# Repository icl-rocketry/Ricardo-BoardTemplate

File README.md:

# Ricardo Board Template
This is a KiCad template including the required components for an ESP32S3 with a USB-C port, a CAN transceiver, as well as logic power input regulation. This is the bare minimum needed for boards in the ricardo ecosystem. If you have followed the [hardware library usage instructions](https://github.com/icl-rocketry/iclr-hw), the hardware libraries will automatically be added to every project started from this template.

## Usage
To use this, clone this repository in your KiCad user templates folder.

By default, this folder is:

MacOS - ```/Users/{USERNAME}/Documents/KiCad/8.0/template/```

Windows -  ```%USERPROFILE%/Documents/KiCad/8.0/template```

Linux - ```/home/{USERNAME}/.local/share/kicad/8.0/template```

Then, you will be able to access the template when making a new project in ```KiCad -> File -> New Project from Template... -> User Templates```

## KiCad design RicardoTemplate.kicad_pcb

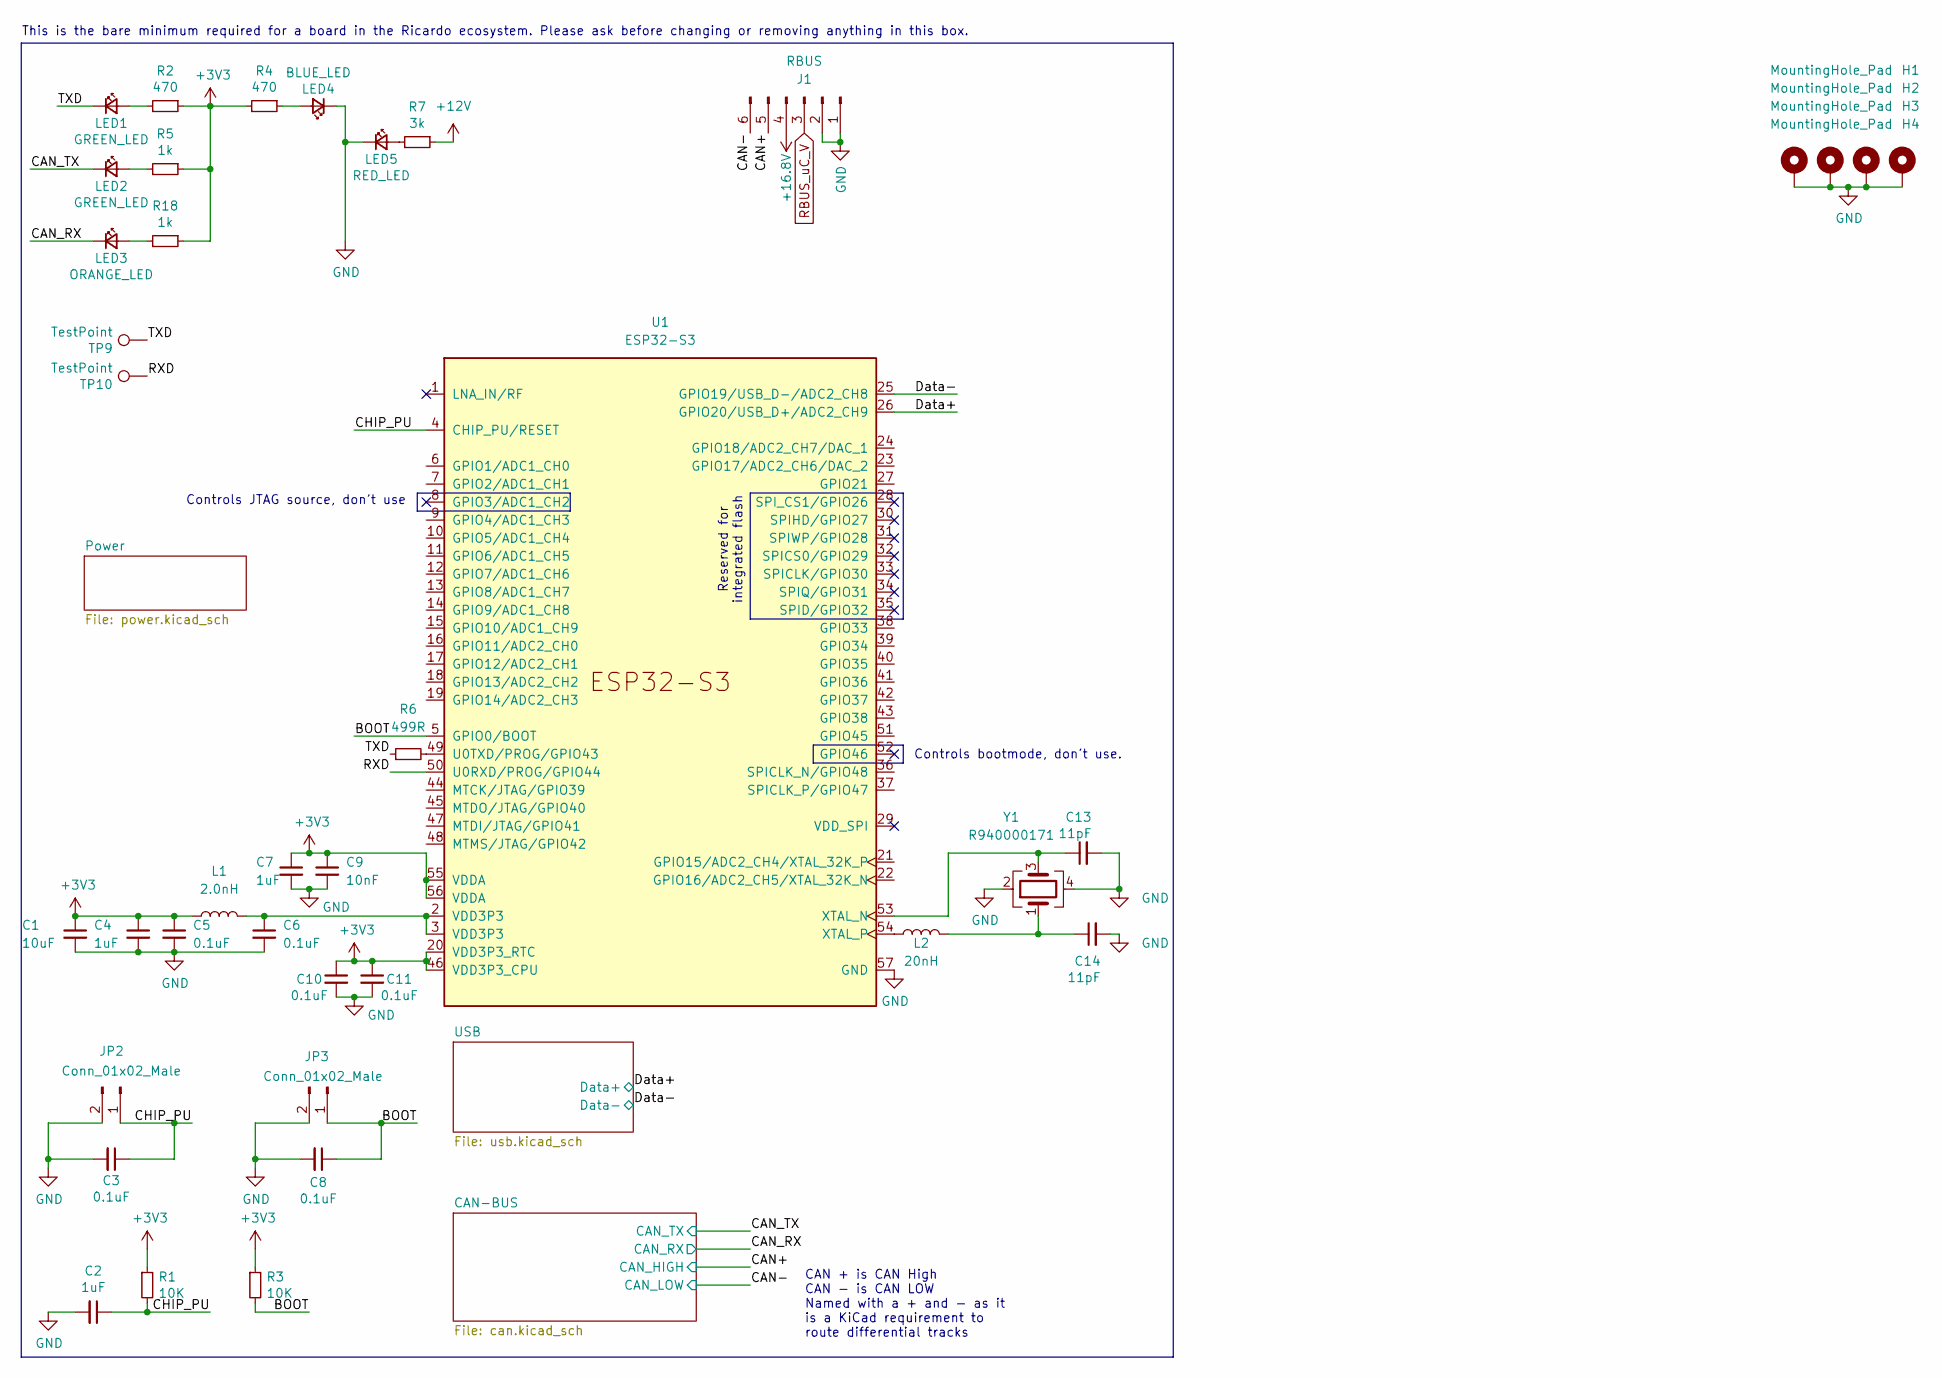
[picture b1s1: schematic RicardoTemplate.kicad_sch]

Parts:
C1: 10uF; C_0402_1005Metric
C2, C4, C7: 1uF; C_0402_1005Metric
C3, C5, C6, C8, C10, C11: 0.1uF; C_0402_1005Metric
C9: 10nF; C_0402_1005Metric
C13, C14: 11pF; C_0402_1005Metric
H1, H2, H3, H4: MountingHole_Pad; MountingHole_3.2mm_M3_DIN965_Pad
J1: RBUS; Molex_Mini-Fit_Jr_5569-06A2_2x03_P4.20mm_Horizontal
JP2, JP3: Conn_01x02_Male; PinHeader_1x02_P2.54mm_Vertical
L1: 2.0nH; L_0402_1005Metric
L2: 20nH; L_0402_1005Metric
LED1, LED2: GREEN_LED; LED_0402_1005Metric
LED3: ORANGE_LED; LED_0402_1005Metric
LED4: BLUE_LED; LED_0402_1005Metric
LED5: RED_LED; LED_0402_1005Metric
R1, R3: 10K; R_0402_1005Metric
R2, R4: 470; R_0402_1005Metric
R5, R18: 1k; R_0402_1005Metric
R6: 499R; R_0402_1005Metric
R7: 3k; R_0402_1005Metric
TP9, TP10: TestPoint; TestPoint_Pad_D1.0mm
U1: ESP32-S3; QFN40P700X700X90-57N
Y1: R940000171; Crystal_SMD_2016-4Pin_2.0x1.6mm

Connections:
+3V3: C1.1, C4.1, C5.1, C7.1, C9.1, C10.1, C11.1, L1.1, R1.1, R2.1, R3.1, R4.2, R5.1, R18.1, U1.20 (VDD3P3_RTC), U1.46 (VDD3P3_CPU), U1.55 (VDDA), U1.56 (VDDA); also elsewhere on the board
+12V: R7.1
+16.8V: J1.4
/BOOT: C8.1, JP3.1, R3.2, U1.5 (GPIO0/BOOT)
/CAN+: J1.5; also elsewhere on the board
/CAN-: J1.6; also elsewhere on the board
/CAN_RX: LED3.1 (K); also elsewhere on the board
/CAN_TX: LED2.1 (K); also elsewhere on the board
/CHIP_PU: C2.1, C3.1, JP2.1, R1.2, U1.4 (CHIP_PU/RESET)
/Data+: U1.26 (GPIO20/USB_D+/ADC2_CH9); also elsewhere on the board
/Data-: U1.25 (GPIO19/USB_D-/ADC2_CH8); also elsewhere on the board
/RXD: TP10.1, U1.50 (U0RXD/PROG/GPIO44)
/TXD: LED1.1 (K), R6.1, TP9.1
GND: C1.2, C2.2, C3.2, C4.2, C5.2, C6.2, C7.2, C8.2, C9.2, C10.2, C11.2, C13.2, C14.2, H1.1, H2.1, H3.1, H4.1, J1.1, J1.2, JP2.2, JP3.2, LED4.1 (K), LED5.1 (K), U1.57 (GND), Y1.2, Y1.4; also elsewhere on the board
unnamed: C6.1, L1.2, U1.2 (VDD3P3), U1.3 (VDD3P3)
unnamed: C14.1, L2.2, Y1.1
unnamed: LED1.2 (A), R2.2
unnamed: LED2.2 (A), R5.2
unnamed: LED3.2 (A), R18.2
unnamed: LED4.2 (A), R4.1
unnamed: LED5.2 (A), R7.2
unnamed: R6.2, U1.49 (U0TXD/PROG/GPIO43)
unnamed: C13.1, U1.53 (XTAL_N), Y1.3
unnamed: L2.1, U1.54 (XTAL_P)
RBUS_uC_V: J1.3; also elsewhere on the board

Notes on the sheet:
Controls bootmode, don't use.
This is the bare minimum required for a board in the Ricardo ecosystem. Please ask before changing or removing anything in this box.
CAN + is CAN High CAN - is CAN LOW Named with a + and - as it is a KiCad requirement to route differential tracks
Controls JTAG source, don't use
Reserved for integrated flash

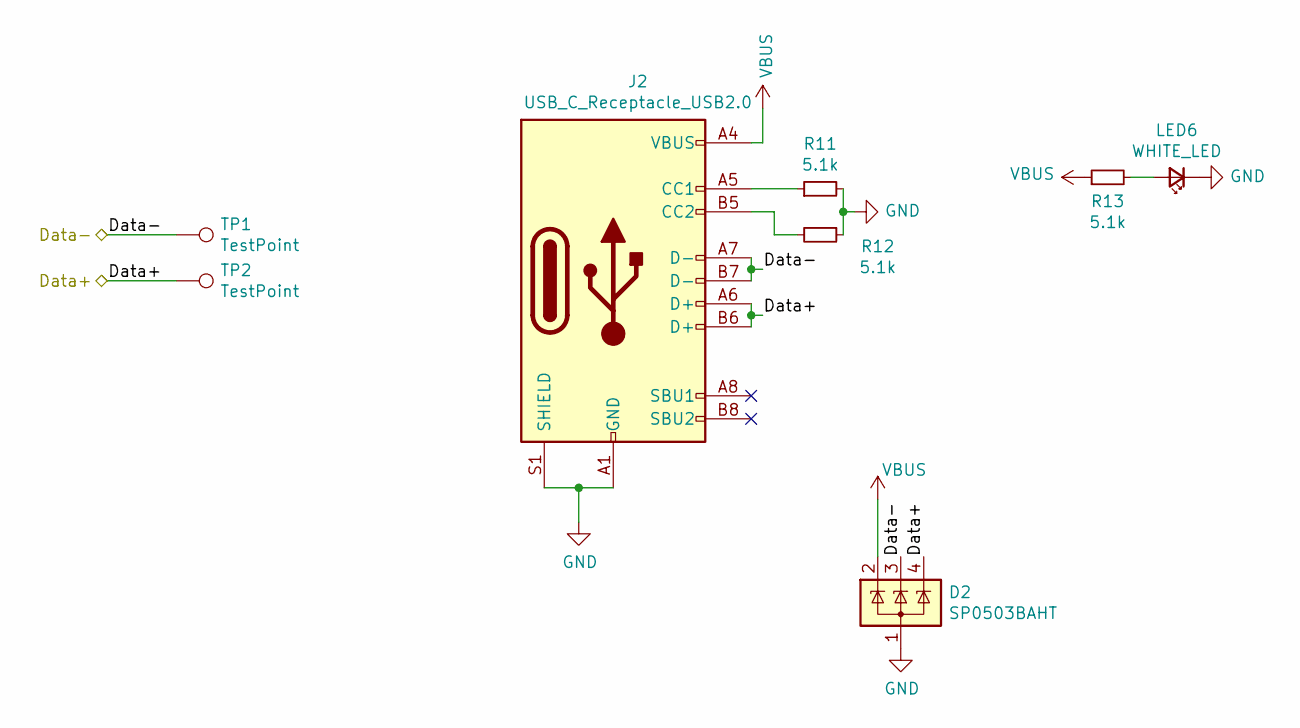
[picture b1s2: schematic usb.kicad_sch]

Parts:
D2: SP0503BAHT; SOT-143
J2: USB_C_Receptacle_USB2.0; USB_C_Receptacle_Palconn_UTC16-G
LED6: WHITE_LED; LED_0402_1005Metric
R11, R12, R13: 5.1k; R_0402_1005Metric
TP1, TP2: TestPoint; TestPoint_Pad_D1.0mm

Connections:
/Data+: D2.4 (K), J2.A6 (D+), J2.B6 (D+), TP2.1; also elsewhere on the board
/Data-: D2.3 (K), J2.A7 (D-), J2.B7 (D-), TP1.1; also elsewhere on the board
GND: D2.1 (A), J2.A1 (GND), J2.A12 (GND), J2.B1 (GND), J2.B12 (GND), J2.S1 (SHIELD), LED6.1 (K), R11.2, R12.1; also elsewhere on the board
unnamed: J2.A5 (CC1), R11.1
unnamed: J2.B5 (CC2), R12.2
unnamed: LED6.2 (A), R13.2
VBUS: D2.2 (K), J2.A4 (VBUS), J2.A9 (VBUS), J2.B4 (VBUS), J2.B9 (VBUS), R13.1; also elsewhere on the board

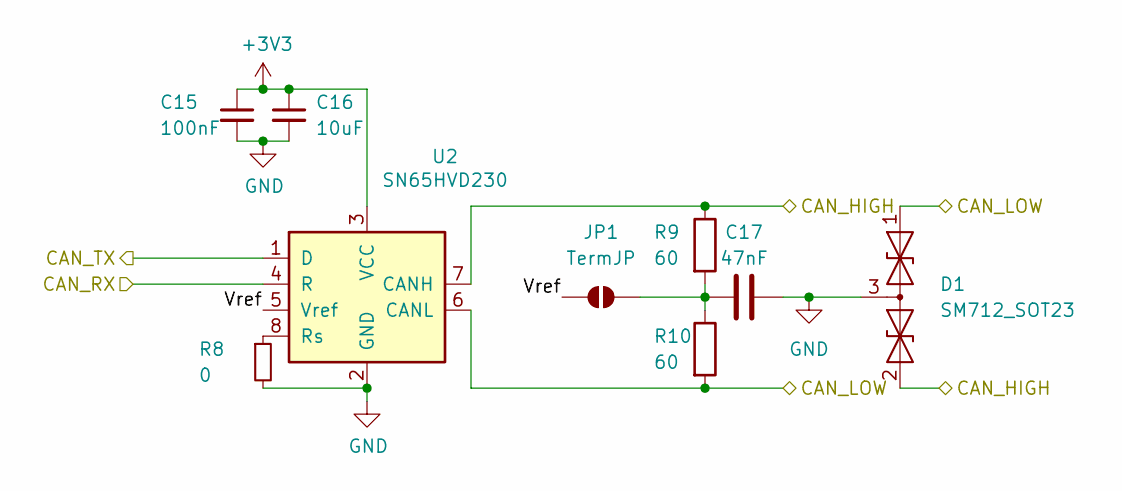
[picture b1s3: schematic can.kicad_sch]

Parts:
C15: 100nF; C_0402_1005Metric
C16: 10uF; C_0402_1005Metric
C17: 47nF; C_0402_1005Metric
D1: SM712_SOT23; SOT-23
JP1: TermJP; SmallerSolderJP
R8: 0; R_0603_1608Metric
R9, R10: 60; R_0603_1608Metric
U2: SN65HVD230; SOIC-8_3.9x4.9mm_P1.27mm

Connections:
+3V3: C15.1, C16.1, U2.3 (VCC); also elsewhere on the board
/CAN+: D1.2 (A2), R9.1, U2.7 (CANH); also elsewhere on the board
/CAN-: D1.1 (A1), R10.2, U2.6 (CANL); also elsewhere on the board
/CAN-BUS/Vref: JP1.1 (A), U2.5 (Vref)
/CAN_RX: U2.4 (R); also elsewhere on the board
/CAN_TX: U2.1 (D); also elsewhere on the board
GND: C15.2, C16.2, C17.2, D1.3 (common), R8.2, U2.2 (GND); also elsewhere on the board
unnamed: C17.1, JP1.2 (B), R9.2, R10.1
unnamed: R8.1, U2.8 (Rs)

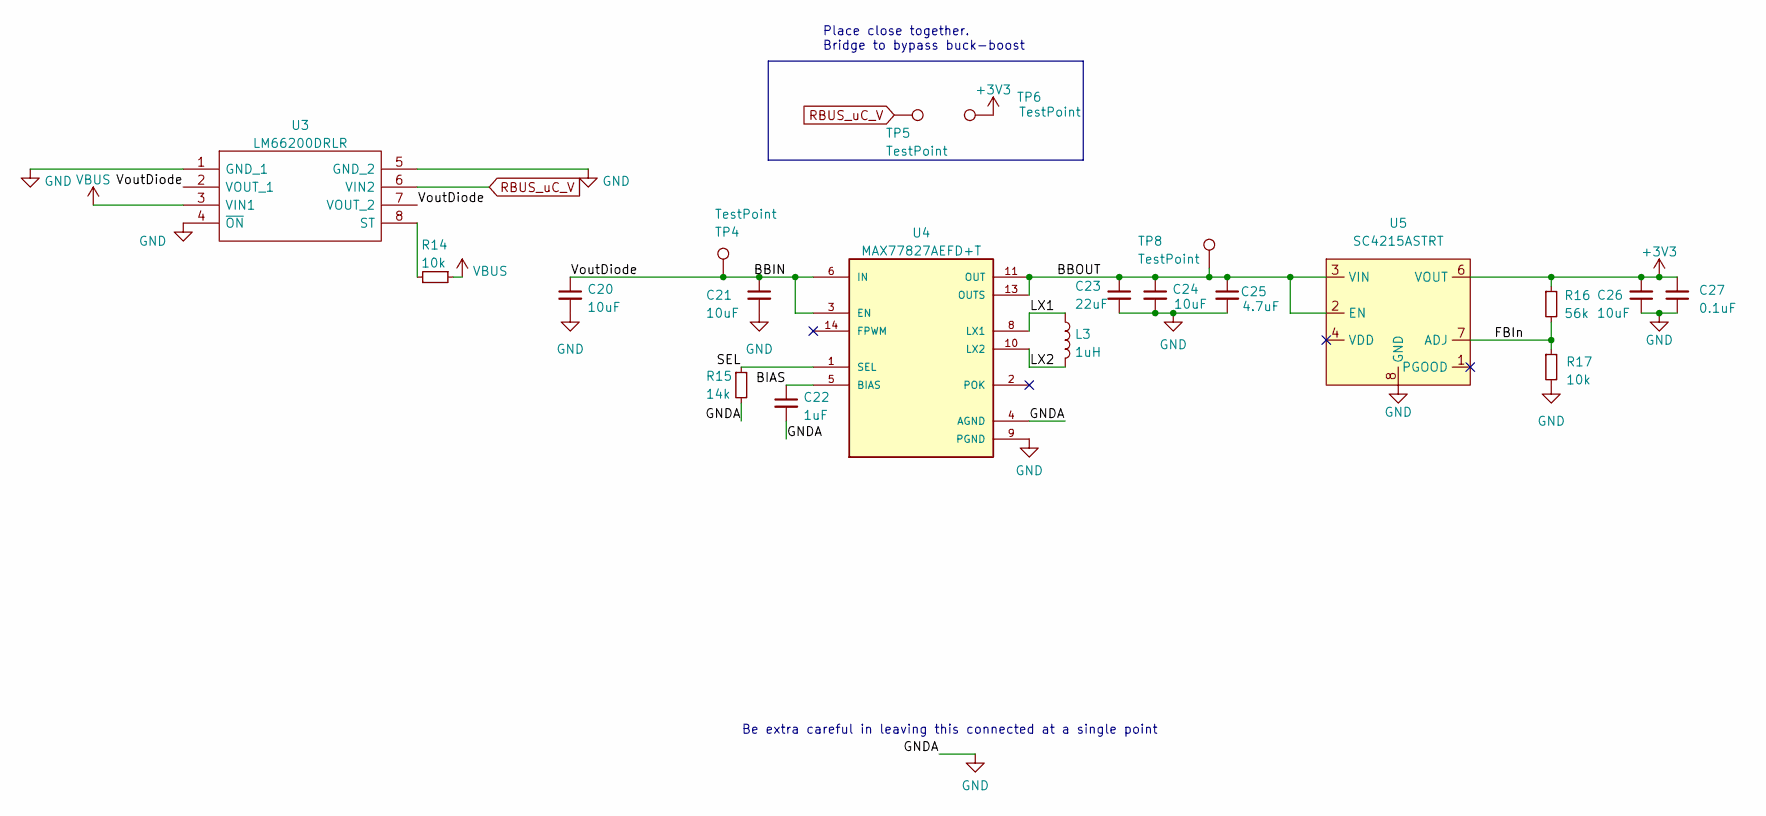
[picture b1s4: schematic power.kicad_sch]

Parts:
C20, C24, C26: 10uF; C_0402_1005Metric
C21: 10uF; C_0603_1608Metric
C22: 1uF; C_0402_1005Metric
C23: 22uF; C_0603_1608Metric
C25: 4.7uF; C_0402_1005Metric
C27: 0.1uF; C_0402_1005Metric
L3: 1uH; L_0805_2012Metric
R14, R17: 10k; R_0402_1005Metric
R15: 14k; R_0402_1005Metric
R16: 56k; R_0402_1005Metric
TP4, TP5, TP6, TP8: TestPoint; TestPoint_Pad_D1.5mm
U3: LM66200DRLR; SOTFL50P160X60-8N; Manufacturer_Part_Number LM66200DRLR; Mouser Part Number 595-LM66200DRLR
U4: MAX77827AEFD+T; CONV_MAX77827AEFD+T; PARTREV B
U5: SC4215ASTRT; SOIC127P599X175-9N

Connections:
+3V3: C26.2, C27.2, R16.1, TP6.1, U5.6 (VOUT); also elsewhere on the board
/Power/BBIN: C20.1, C21.1, TP4.1, U3.2 (VOUT_1), U3.7 (VOUT_2), U4.3 (EN), U4.6 (IN)
/Power/BBOUT: C23.1, C24.1, C25.1, TP8.1, U4.11 (OUT), U4.13 (OUTS), U5.2 (EN), U5.3 (VIN)
/Power/BIAS: C22.1, U4.5 (BIAS)
/Power/FBIn: R16.2, R17.1, U5.7 (ADJ)
/Power/LX1: L3.1, U4.8 (LX1)
/Power/LX2: L3.2, U4.10 (LX2)
/Power/SEL: R15.1, U4.1 (SEL)
GND: C20.2, C21.2, C22.2, C23.2, C24.2, C25.2, C26.1, C27.1, R15.2, R17.2, U3.1 (GND_1), U3.4 (~ON), U3.5 (GND_2), U4.4 (AGND), U4.9 (PGND), U5.8 (GND), U5.9 (GND); also elsewhere on the board
unnamed: R14.2, U3.8 (ST)
RBUS_uC_V: TP5.1, U3.6 (VIN2); also elsewhere on the board
VBUS: R14.1, U3.3 (VIN1); also elsewhere on the board

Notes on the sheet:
Place close together. Bridge to bypass buck-boost
Be extra careful in leaving this connected at a single point

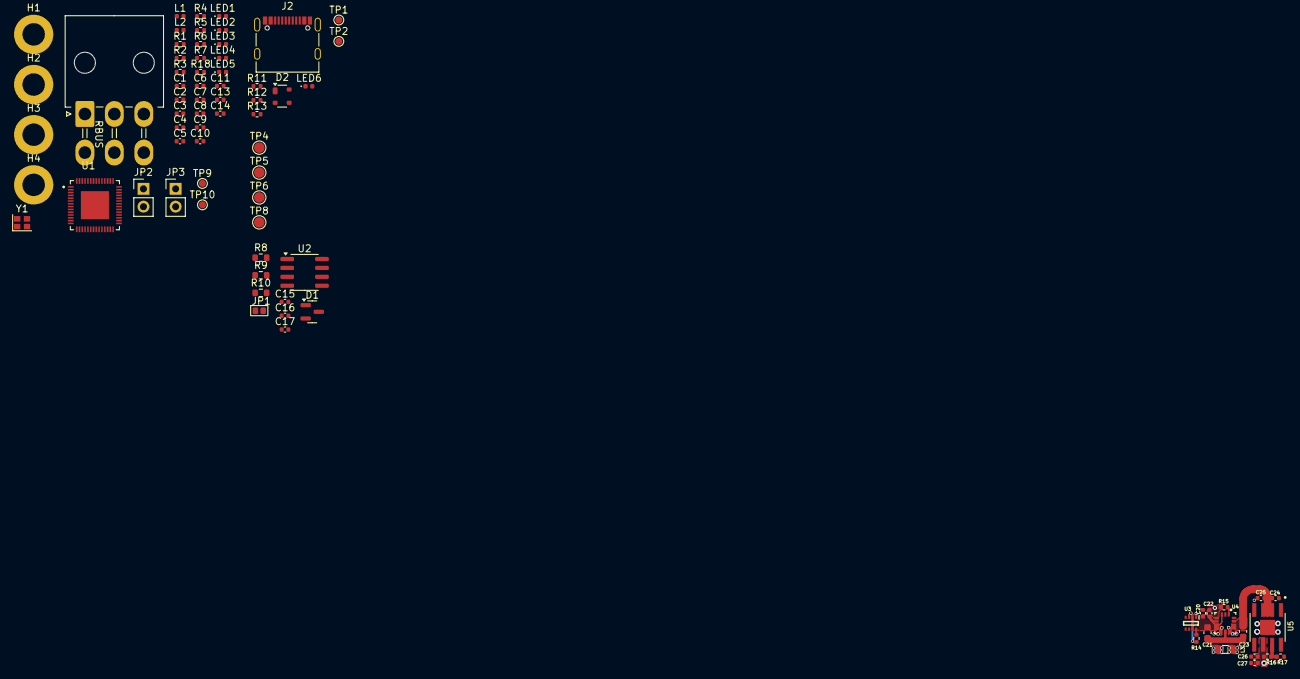
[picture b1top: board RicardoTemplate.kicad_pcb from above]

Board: 4 copper layers, 76 parts (0 on the bottom side), 38 nets.

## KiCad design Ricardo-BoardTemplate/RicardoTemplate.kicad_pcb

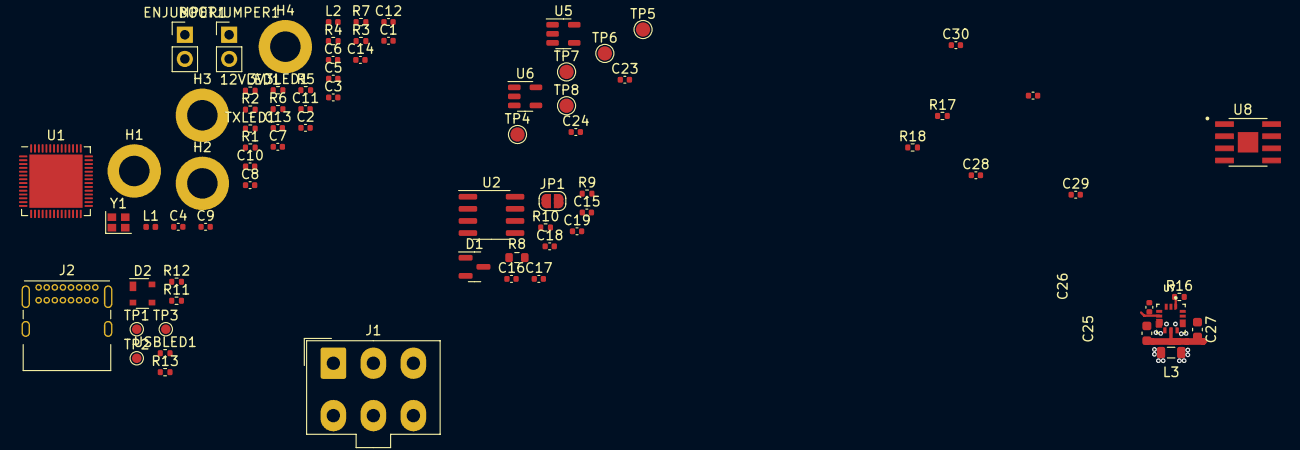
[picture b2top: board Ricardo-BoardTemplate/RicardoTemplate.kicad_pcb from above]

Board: 2 copper layers, 77 parts (0 on the bottom side), 36 nets.

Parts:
3V3LED1: 3V3LED; R_0402_1005Metric
12VLED1: 12V_LED; R_0402_1005Metric
BOOTJUMPER1: Conn_01x02_Male; PinHeader_1x02_P2.54mm_Vertical
C1, C16, C28, C30: 10uF; C_0402_1005Metric
C2, C4, C7, C26: 1uF; C_0402_1005Metric
C3, C5, C6, C8, C10, C11, C17, C31: 0.1uF; C_0402_1005Metric
C9: 10nF; C_0402_1005Metric
C12: 4.2pF; C_0402_1005Metric
C13, C14: C; C_0402_1005Metric
C15: 100nF; C_0402_1005Metric
C18, C19: 220pF; C_0402_1005Metric
C23, C24, C29: 4.7uF; C_0402_1005Metric
C25: 10uF; C_0603_1608Metric
C27: 22uF; C_0603_1608Metric
D1: SM712_SOT23; SOT-23
D2: SP0503BAHT; SOT-143
ENJUMPER1: Conn_01x02_Male; PinHeader_1x02_P2.54mm_Vertical
H1, H2, H3, H4: MountingHole_Pad; MountingHole_3.2mm_M3_DIN965_Pad
J1: RBUS; Molex_Mini-Fit_Jr_5566-06A_2x03_P4.20mm_Vertical
J2: USB_C_Receptacle_USB2.0; USB_C_Receptacle_GCT_USB4085
JP1: TermJP; SolderJumper-2_P1.3mm_Open_RoundedPad1.0x1.5mm
L1: 2.0nH; L_0402_1005Metric
L2: 20nH; L_0402_1005Metric
L3: 1uH; L_0805_2012Metric
R1, R3: 10K; R_0402_1005Metric
R2, R4, R13: 470; R_0402_1005Metric
R5: 47.5; R_0402_1005Metric
R6: 499; R_0402_1005Metric
R7: 3k; R_0402_1005Metric
R8: 0; R_0603_1608Metric
R9, R10: 60; R_0402_1005Metric
R11, R12: 5.1k; R_0402_1005Metric
R16: 14k; R_0402_1005Metric
R17: 56k; R_0402_1005Metric
R18: 10k; R_0402_1005Metric
TP1, TP2, TP3: TestPoint; TestPoint_Pad_D1.0mm
TP4, TP5, TP6, TP7, TP8: TestPoint; TestPoint_Pad_D1.5mm
TXLED1: TX_LED; R_0402_1005Metric
U1: ESP32-S3; QFN-56-1EP_7x7mm_P0.4mm_EP5.6x5.6mm
U2: SN65HVD230; SOIC-8_3.9x4.9mm_P1.27mm
U5, U6: LM66100; SOT-23-5
U7: MAX77827AEFD+T; CONV_MAX77827AEFD+T
U8: SC4215; SOIC127P599X175-9N
USBLED1: USB_LED; R_0402_1005Metric
Y1: 40MHz±10ppm; Crystal_SMD_2016-4Pin_2.0x1.6mm

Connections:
+3V3: C1.1, C4.1, C5.1, C7.1, C9.1, C10.1, C11.1, C15.1, C16.1, C30.2, C31.2, L1.1, R1.1, R2.1, R3.1, R4.2, R17.1, TP6.1, U1.20 (VDD3P3_RTC), U1.46 (VDD3P3_CPU), U1.55 (VDDA), U1.56 (VDDA), U2.3 (VCC), U8.6 (VOUT)
+12V: J1.4, R7.1
/BOOT: BOOTJUMPER1.1, C8.1, R3.2, U1.5 (GPIO0/BOOT)
/CAN+: C18.2, D1.2 (A2), J1.5, R9.1, U2.7 (CANH)
/CAN-: C19.2, D1.1 (A1), J1.6, R10.2, U2.6 (CANL)
/CAN-BUS/Vref: JP1.1 (A), U2.5 (Vref)
/CHIP_PU: C2.1, C3.1, ENJUMPER1.1, R1.2, U1.4 (CHIP_PU/RESET)
/Data+: D2.4 (K), J2.A6 (D+), J2.B6 (D+), TP2.1, U1.26 (GPIO20/USB_D+/ADC2_CH9)
/Data-: D2.3 (K), J2.A7 (D-), J2.B7 (D-), TP1.1, U1.25 (GPIO19/USB_D-/ADC2_CH8)
/Power/BBIN: C23.1, C24.1, C25.1, TP4.1, U5.5 (OUT), U6.5 (OUT), U7.3 (EN), U7.6 (IN)
/Power/BBOUT: C27.1, C28.1, C29.1, TP8.1, U7.11 (OUT), U7.13 (OUTS), U8.2 (EN), U8.3 (VIN)
/Power/BIAS: C26.1, U7.5 (BIAS)
/Power/FBIn: R17.2, R18.1, U8.7 (ADJ)
/Power/LX1: L3.1, U7.8 (LX1)
/Power/LX2: L3.2, U7.10 (LX2)
/Power/SEL: R16.1, U7.1 (SEL)
/TXD: R6.1, TXLED1.1 (K)
GND: 3V3LED1.1 (K), 12VLED1.1 (K), BOOTJUMPER1.2, C1.2, C2.2, C3.2, C4.2, C5.2, C6.2, C7.2, C8.2, C9.2, C10.2, C11.2, C13.2, C14.2, C15.2, C16.2, C17.2, C18.1, C19.1, C23.2, C24.2, C25.2, C27.2, C28.2, C29.2, C30.1, C31.1, D1.3 (common), D2.1 (A), ENJUMPER1.2, H1.1, H2.1, H3.1, H4.1, J1.1, J1.2, J2.A1 (GND), J2.A12 (GND), J2.B1 (GND), J2.B12 (GND), J2.S1 (SHIELD), R5.1, R8.2, R11.2, R12.1, R18.2, U1.57 (GND), U2.2 (GND), U5.2 (GND), U5.3 (CTL), U6.2 (GND), U6.3 (CTL), U7.9 (PGND), U8.8 (GND), U8.9 (GND), USBLED1.1 (K), Y1.2, Y1.4
GNDA: C26.2, R16.2, U7.4 (AGND)
unnamed: 3V3LED1.2 (A), R4.1
unnamed: 12VLED1.2 (A), R7.2
unnamed: C6.1, L1.2, U1.2 (VDD3P3), U1.3 (VDD3P3)
unnamed: C12.1, R5.2
unnamed: C12.2, U1.1 (LNA_IN/RF)
unnamed: C13.1, U1.53 (XTAL_N), Y1.3
unnamed: C14.1, L2.2, Y1.1
unnamed: C17.1, JP1.2 (B), R9.2, R10.1
unnamed: J2.A5 (CC1), R11.1
unnamed: J2.B5 (CC2), R12.2
unnamed: L2.1, U1.54 (XTAL_P)
unnamed: R2.2, TXLED1.2 (A)
unnamed: R8.1, U2.8 (Rs)
unnamed: R13.2, USBLED1.2 (A)
unnamed: R6.2, U1.49 (U0TXD/PROG/GPIO43)
RBUS_uC_V: J1.3, TP5.1, U5.1 (IN)
VBUS: D2.2 (K), J2.A4 (VBUS), J2.A9 (VBUS), J2.B4 (VBUS), J2.B9 (VBUS), R13.1, TP3.1, TP7.1, U6.1 (IN)

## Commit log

2022-11-04 most FP assignments to 0402
2022-11-19 Finished power schematic, layout template still left to do.
2022-11-22 Initial buck boost layout
2022-11-26 Changed folder structure, template layout for buck boost and LDO
2022-12-21 updated ideal oring diode and layout
2022-12-23 Added U0TXD and U0RXD test points
2023-01-21 changed capacitor value and resistor footprints
2023-02-09 changed usb port footprint to the combined SMD/THT one
2023-02-21 Fixed zone priorities and other small things
2023-03-14 updated some schematic values
2023-11-11 implemented fixes that were changed for ordering of nimbus flight electronics, tidied up layout and set up manufacturing constraints
2023-11-11 esp32 s3 better footprint
2024-11-02 Added CAN LEDs and some general fixes noticed over the year
2024-11-02 Readme update
2025-01-20 Changed minifit Jr footprint to horizontal
2025-02-01 Fixed LED footprints assigned as resistors, added gitignore for locks and backups
2025-02-01 Ignore .prl files
2025-03-13 Fix: Remove fp-info-cache
2025-06-28 Fixed some footprint assignments, tidies up layout
